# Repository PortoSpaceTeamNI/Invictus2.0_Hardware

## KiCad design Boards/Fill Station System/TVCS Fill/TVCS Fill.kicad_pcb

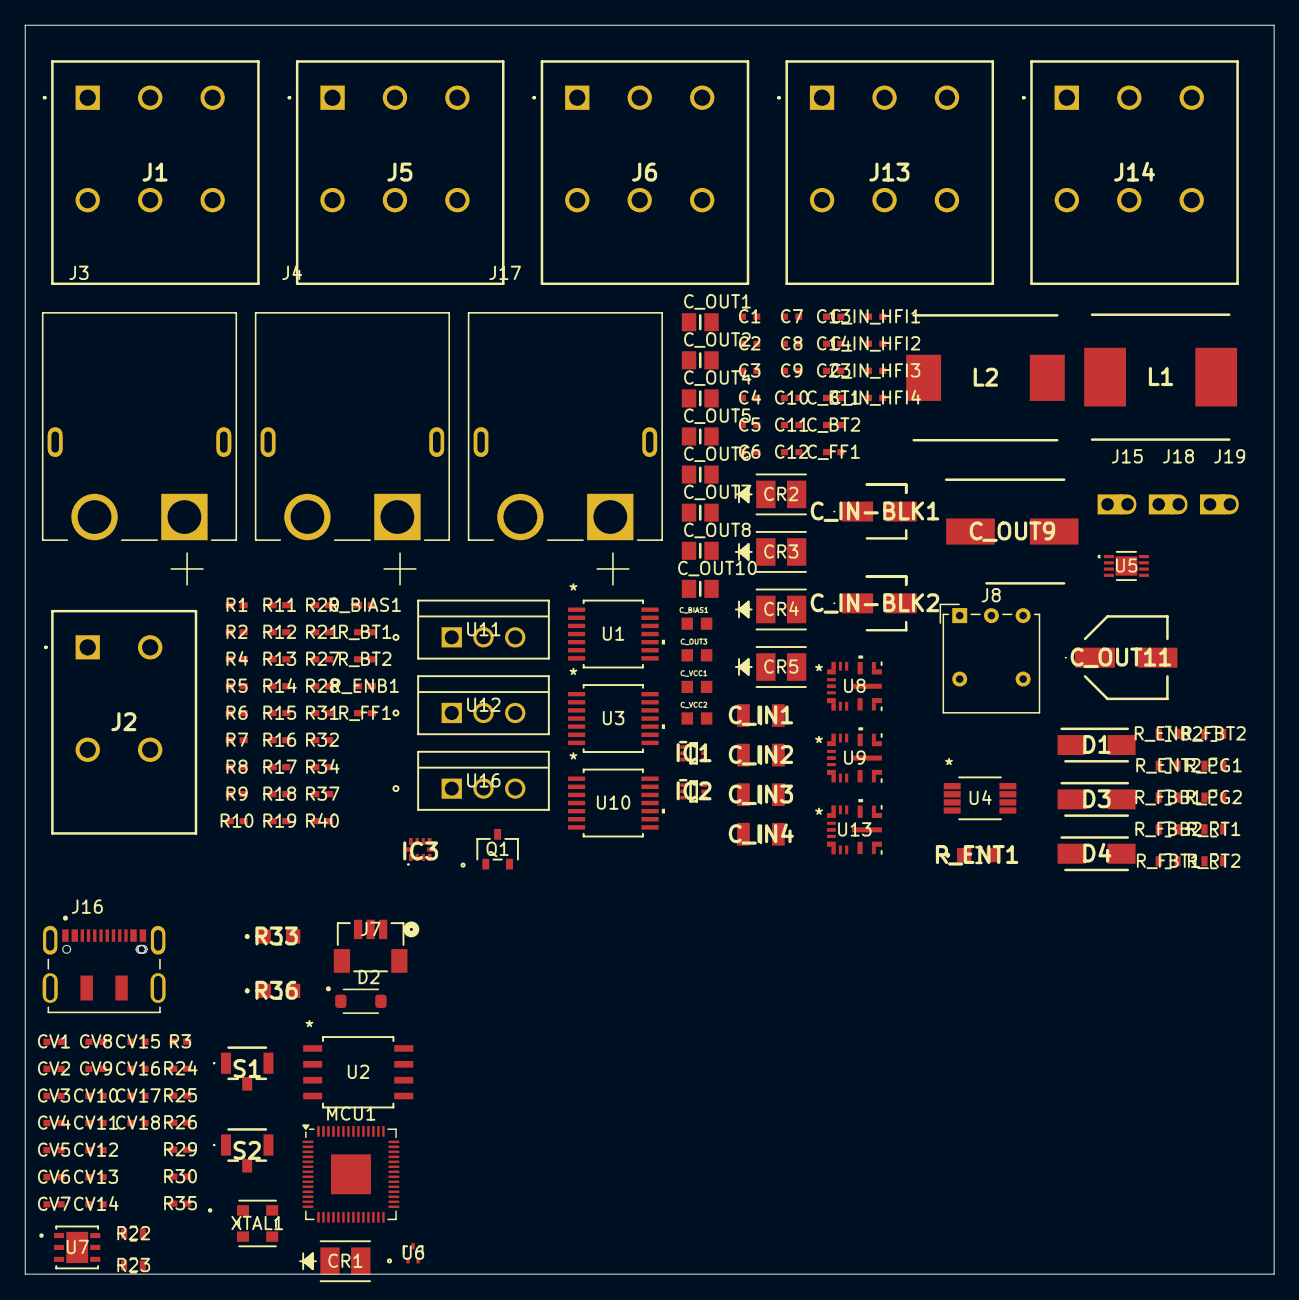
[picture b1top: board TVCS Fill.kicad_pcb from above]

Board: 6 copper layers, 100.0 x 100.0 mm, 162 parts (0 on the bottom side), 99 nets, no tracks yet.

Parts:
C1, C3, C9, C23: 100nF; Capacitor_0402
C2, C4, C5, C6, C7, C8, C10, C12, C13, C14: 10nF; Capacitor_0402
C11: 100 nF; Capacitor_0402
CR1, CR2, CR3, CR4, CR5: VLMC3100-GS08; LED_PLCC_VSMB
CV1, CV3, CV6, CV13, CV17: 1uF; Capacitor_0402
CV2, CV4, CV5, CV7, CV8, CV9, CV10, CV11, CV12, CV14, CV18: 100nF; Capacitor_0402
CV15, CV16: 4.7uF; Capacitor_0402
C_BIAS1: 1u; Capacitor_0603
C_BT1, C_BT2: 100n; Capacitor_0402
C_FF1: 22p; Capacitor_0402
C_IN1, C_IN2, C_IN3, C_IN4: 4.7u; Capacitor_1206
C_IN-BLK1, C_IN-BLK2: 10u; Capacitor_4mm
C_IN_HFI1, C_IN_HFI2, C_IN_HFI3, C_IN_HFI4: 100n; Capacitor_0402
C_OUT1, C_OUT2, C_OUT5, C_OUT7: 22u; Capacitor_0805
C_OUT3: 1u; Capacitor_0603
C_OUT4, C_OUT6, C_OUT8, C_OUT10: 10u; Capacitor_0805
C_OUT9: 560u; Capacitor_8mm
C_OUT11: 100u; Capacitor_6mm
C_VCC1, C_VCC2: 1u; Capacitor_0603
D1, D3, D4: RSX301L-30DDTE25; DIOM5026X220N
D2: PMEG2010ER; SODFL3517X110N
IC1, IC2: NSVT30010MXV6T1G; SOTFL50P160X60-6N
IC3: ADS1115IRUGR
J1, J5, J6, J13, J14: 1190298
J2: 1190297
J3, J4, J17: XT60PW-M; AMASS_XT60PW-M
J7: BM03B-SRSS-TBLFSN; CONN_BM03B-SRSS-TBLFSN_JST
J8: XT60PW-M; SW_Lever_1P2T_NKK_GW12LxH
J15, J18, J19: Conn_01x01_Socket; Pico_01pin
J16: DX07S016JA1R1500; JAE_DX07S016JA1R1500
L1: 15u; Inductor_10.1x10
L2: 10u; Inductor_11.5x10
MCU1: RP2040; QFN-56-1EP_7x7mm_P0.4mm_EP3.2x3.2mm
Q1: 2N7002H6327XTSA2; PG-SOT23-3-5_INF_MIN
R1, R2, R6, R7, R16, R18, R24, R25: 100; RES_0402
R3, R21, R26, R27, R28, R32, R35: 1k; RES_0402
R4: 200k; RES_0402
R5, R15, R19, R20, R31, R34, R40: 2k; RES_0402
R8: 120; RES_0402
R9, R10: 20K; RES_0402
R11, R12, R13: 10K; RES_0402
R14, R17, R29, R37: 10k; RES_0402
R22, R23: 27; RES_0603
R30: 665; RES_0402
R33, R36: 5k1; RES_0805
R_BIAS1: 10; RES_0402
R_BT1: 100; RES_0402
R_BT2: 50; RES_0402
R_ENB1: 35k; RES_0402
R_ENB2: 100k; RES_0603
R_ENT1: 400k; RES_0805
R_ENT2: 1.15M; RES_0603
R_FBB1: 24k9; RES_0603
R_FBB2: 9k09; RES_0603
R_FBT1, R_FBT2: 100K; RES_0603
R_FF1: 1k; RES_0402
R_PG1, R_PG2: 100K; RES_0603
R_RT1, R_RT2: 33k2; RES_0603
S1, S2: TL1017AABF160QG
U1, U3: MAX31856MUD+T; 21-0066J_14_MXM
U2: W25Q128JVSIQ TR; SOIC_208MIL_WIN
U4: PCA9306DP_118; TSSOP8_SOT505-1_NXP
U5: MAX485CSA+T; DFN8_2x3MC_MCH
U6: ESD7L5.0DT5G; SOT-723_0P85X1P25_ONS
U7: ST1L05APU33R; DFN_5APU33R_STM
U8: MCP9808T-E/MC; VQFN-HR14_RJR_TEX
U9: MAX31856MUD+T; VQFN-HR14_RJR_TEX
U10: LM61460AASQRJRRQ1; 21-0066J_14_MXM
U11, U12, U16: IRLZ44NPBF; PG-TO220-3_INF
U13: LM61460AASQRJRRQ1; VQFN-HR14_RJR_TEX
XTAL1: ASE-12.000MHZ-LC-T; ASE-3.2X2.5_ABR

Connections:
+3.3V: C5.2, C6.2, C7.2, C8.2, C12.2, C13.2, C14.1, CV5.1, CV6.1, CV7.1, CV8.1, CV9.1, CV10.1, CV11.1, CV12.1, CV13.1, CV14.1, CV16.2, CV18.1, MCU1.1 (IOVDD), MCU1.10 (IOVDD), MCU1.22 (IOVDD), MCU1.33 (IOVDD), MCU1.42 (IOVDD), MCU1.43 (ADC_AVDD), MCU1.44 (VREG_IN), MCU1.48 (USB_VDD), MCU1.49 (IOVDD), Q1.1 (G), R3.1, R11.1, R12.1, R13.2, R15.1, R19.1, R20.1, R29.2, R31.1, U1.5 (AVDD), U1.8 (DVDD), U2.8 (VCC), U3.5 (AVDD), U3.8 (DVDD), U4.2 (VREF1), U7.2 (V0), U8.8 (VDD), U9.5 (AVDD), U9.8 (DVDD), XTAL1.4 (VDD)
+5V: C11.1, CR2.2, CR3.2, CR4.2, CR5.2, IC3.8 (VDD), R4.2, R5.1, R9.1, R34.1, R40.1, U5.8 (VCC)
+12V: C_OUT3.1, C_OUT4.1, C_OUT6.1, C_OUT8.1, C_OUT10.1, C_OUT11.1, D1.1 (K), D3.1 (K), D4.1 (K), J3.2 (-), J4.2 (-), J5.1, J5.2, J13.1, J13.2, J14.1, J14.2, J17.2 (-), L2.2, R_FBT2.1, R_PG2.2
+16V: C_IN1.1, C_IN2.1, C_IN3.1, C_IN4.1, C_IN-BLK1.1, C_IN-BLK2.1, C_IN_HFI1.1, C_IN_HFI2.1, C_IN_HFI3.1, C_IN_HFI4.1, J8.2 (-), R_ENT1.2, R_ENT2.2, U10.8 (VIN1), U10.12 (VIN2), U13.8 (VIN1), U13.12 (VIN2)
/5V REG: C_OUT1.1, C_OUT2.1, C_OUT5.1, C_OUT7.1, C_OUT9.1, L1.2, R_BIAS1.2, R_FBT1.1, R_FF1.1, R_PG1.2
/ADC RDY: Q1.2 (S), R31.2
/ADC_AIN0: IC3.4 (AIN0), J5.3, J5.4
/ADC_AIN1: IC3.5 (AIN1), J13.3, J13.4
/ADC_AIN2: IC3.6 (AIN2), J14.3, J14.4
/DC.DC1 PGOOD: C_VCC2.1, R_PG2.1, U13.2 (VCC), U13.5 (PGOOD)
/DC.DC2 PGOOD: C_VCC1.1, R_PG1.1, U10.2 (VCC), U10.5 (PGOOD)
/RP2040 Standard/+5V: CV15.2, CV17.2, D2.C, U7.3 (V1)
/RP2040 Standard/GP27_ADC1: J15.1, MCU1.39 (GPIO27_ADC1)
/RP2040 Standard/GP28_ADC2: J18.1, MCU1.40 (GPIO28_ADC2)
/RP2040 Standard/GP29_ADC3: J19.1, MCU1.41 (GPIO29_ADC3)
/RP2040 Standard/MCU QSPI_SCLK: MCU1.52 (QSPI_SCLK), U2.6 (CLK)
/RP2040 Standard/MCU QSPI_SD0: MCU1.53 (QSPI_SD0), U2.5 (DI(IO0))
/RP2040 Standard/MCU QSPI_SD1: MCU1.55 (QSPI_SD1), U2.2 (DO(IO1))
/RP2040 Standard/MCU QSPI_SD2: MCU1.54 (QSPI_SD2), U2.3 (/WP(IO2))
/RP2040 Standard/MCU QSPI_SD3: MCU1.51 (QSPI_SD3), U2.7 (/HOLD_/RESET)
/RP2040 Standard/MCU QSPI_SS: MCU1.56 (QSPI_SS), R35.2, U2.1 (/CS)
/RP2040 Standard/USB_DM: J16.5 (D-), J16.8 (D-), R23.1, U6.1
/RP2040 Standard/USB_DP: J16.6 (D+), J16.7 (D+), R22.1, U6.2
/RP2040 Standard/~RST: R26.1, S1.2 (NO)
/RP2040 Standard/~USB_BOOT: R35.1, S2.2 (NO)
/RS_ENABLE: IC2.2 (B2), R12.2, U5.2 (*RE), U5.3 (DE)
/RS_RX: R11.2, U5.1 (RO)
/RS_TX: R13.1, U5.4 (DI)
/SPI_MISO: U1.11 (SDO), U3.11 (SDO), U9.11 (SDO)
/SPI_MOSI: U1.12 (SDI), U3.12 (SDI), U9.12 (SDI)
/SPI_SCK: U1.10 (SCK), U3.10 (SCK), U9.10 (SCK)
/TEMP ALERT: R15.2, U8.3 (ALERT)
/TEMP SDA I2C: R20.2, U8.1 (SDA)
/TEMP SDL I2C: R19.2, U8.2 (SCL)
/THERMO1 T+: J1.1, J1.2, R1.2
/THERMO1 T-: J1.3, J1.4, R2.2, U1.2 (BIAS)
/THERMO1_~CS: IC1.5 (B1), U1.9 (~CS)
/THERMO2 T+: J1.5, J1.6, R6.2
/THERMO2 T-: J6.1, J6.2, R7.2, U3.2 (BIAS)
/THERMO2_~CS: IC1.2 (B2), U3.9 (~CS)
/THERMO3 T+: J6.3, J6.4, R16.2
/THERMO3 T-: J6.5, J6.6, R18.2, U9.2 (BIAS)
/THERMO3_~CS: IC2.5 (B1), U9.9 (~CS)
/Valve Control 1: R17.1, U11.1 (G)
/Valve Control 2: R14.1, U12.1 (G)
/Valve Control 3: R37.1, U16.1 (G)
CRYSTAL: MCU1.20 (XIN), XTAL1.3 (OUTPUT)
GND: C2.2, C4.2, C5.1, C6.1, C7.1, C8.1, C10.2, C11.2, C12.1, C13.1, C14.2, C23.2, CR1.1, CV1.2, CV2.1, CV3.2, CV4.1, CV5.2, CV6.2, CV7.2, CV8.2, CV9.2, CV10.2, CV11.2, CV12.2, CV13.2, CV14.2, CV15.1, CV16.1, CV17.1, CV18.2, C_BIAS1.2, C_IN1.2, C_IN2.2, C_IN3.2, C_IN4.2, C_IN-BLK1.2, C_IN-BLK2.2, C_IN_HFI1.2, C_IN_HFI2.2, C_IN_HFI3.2, C_IN_HFI4.2, C_OUT1.2, C_OUT2.2, C_OUT3.2, C_OUT4.2, C_OUT5.2, C_OUT6.2, C_OUT7.2, C_OUT8.2, C_OUT9.2, C_OUT10.2, C_OUT11.2, C_VCC1.2, C_VCC2.2, IC1.3 (C1), IC1.6 (C2), IC2.3 (C1), IC2.6 (C2), IC3.1 (ADDR), IC3.3 (GND), IC3.7 (AIN3), J5.5, J5.6, J7.2, J8.1 (+), J13.5, J13.6, J14.5, J14.6, J16.1 (GND), J16.12 (GND), MCU1.19 (TESTEN), MCU1.57 (GND), R10.2, R14.2, R17.2, R33.1, R36.1, R37.2, R_ENB1.1, R_ENB2.1, R_FBB1.2, R_FBB2.2, R_RT1.1, R_RT2.1, S1.1 (COM), S1.G1, S2.1 (COM), S2.G1, U1.1 (AGND), U1.14 (DGND), U2.4 (GND), U3.1 (AGND), U3.14 (DGND), U4.1 (GND), U5.5 (GND), U6.3, U7.6 (GND), U7.7 (GND), U8.4 (GND), U8.5 (A2), U8.6 (A1), U8.7 (A0), U8.9 (EPAD), U9.1 (AGND), U9.14 (DGND), U10.3 (AGND), U10.9 (PGND1), U10.11 (PGND2), U11.3 (S), U12.3 (S), U13.1 (BIAS), U13.3 (AGND), U13.9 (PGND1), U13.11 (PGND2), U16.3 (S), XTAL1.2 (GND/CASE)
unnamed: CR1.2, R30.2
unnamed: CR2.1, R21.2
unnamed: CR3.1, R27.2
unnamed: CR4.1, R28.2
unnamed: CR5.1, R32.2
unnamed: C_FF1.1, R_FF1.2
unnamed: D1.2 (A), J4.1 (+), U12.2
unnamed: D2.A, J16.2 (VBUS), J16.11 (VBUS)
unnamed: D3.2 (A), J3.1 (+), U11.2
unnamed: D4.2 (A), J17.1 (+), U16.2
unnamed: IC1.4 (E1), R21.1
unnamed: IC1.1 (E2), R27.1
unnamed: IC2.4 (E1), R28.1
unnamed: IC2.1 (E2), R32.1
unnamed: IC3.2 (ALERT/RDY), Q1.3 (D), R5.2
unnamed: IC3.10 (SCL), R34.2, U4.6 (SCL2)
unnamed: IC3.9 (SDA), R40.2, U4.5 (SDA2)
unnamed: J2.1 (1.1), J2.2 (1.2), R8.1, R10.1, U5.7 (B)
unnamed: J2.3 (2.1), J2.4 (2.2), R8.2, R9.2, U5.6 (A)
unnamed: J7.1, R24.1
unnamed: J7.3, R25.1
unnamed: J16.3 (CC1), R36.2
unnamed: J16.9 (CC2), R33.2
unnamed: MCU1.37 (GPIO25), R30.1
unnamed: CV1.1, MCU1.26 (RUN), R3.2, R26.2
unnamed: MCU1.24 (SWCLK), R24.2
unnamed: MCU1.25 (SWD), R25.2
unnamed: MCU1.46 (USB_DM), R23.2
unnamed: MCU1.47 (USB_DP), R22.2
unnamed: CV2.2, CV3.1, CV4.2, MCU1.23 (DVDD), MCU1.45 (VREG_VOUT), MCU1.50 (DVDD)
unnamed: C1.1, R1.1, U1.4 (T+)
unnamed: C1.2, C2.1, R2.1, U1.3 (T-)
unnamed: C3.1, R6.1, U3.4 (T+)
unnamed: C3.2, C4.1, R7.1, U3.3 (T-)
unnamed: C23.1, R4.1, U4.7 (VREF2), U4.8 (EN)
unnamed: C9.1, R16.1, U9.4 (T+)
unnamed: C9.2, C10.1, R18.1, U9.3 (T-)
unnamed: C_BIAS1.1, R_BIAS1.1, U10.1 (BIAS)
unnamed: C_BT1.2, R_BT1.1, U10.14 (CBOOT)
unnamed: R_ENB1.2, R_ENT1.1, U10.7 (EN/SYNC)
unnamed: C_FF1.2, R_FBB1.1, R_FBT1.2, U10.4 (FB)
unnamed: R_BT1.2, U10.13 (RBOOT)
unnamed: R_RT1.2, U10.6 (RT)
unnamed: C_BT1.1, L1.1, U10.10 (SW)
unnamed: C_BT2.2, R_BT2.1, U13.14 (CBOOT)
unnamed: R_ENB2.2, R_ENT2.1, U13.7 (EN/SYNC)
unnamed: R_FBB2.1, R_FBT2.2, U13.4 (FB)
unnamed: R_BT2.2, U13.13 (RBOOT)
unnamed: R_RT2.2, U13.6 (RT)
unnamed: C_BT2.1, L2.1, U13.10 (SW)
unnamed: R29.1, XTAL1.1 (TRI-STATE(STBY))

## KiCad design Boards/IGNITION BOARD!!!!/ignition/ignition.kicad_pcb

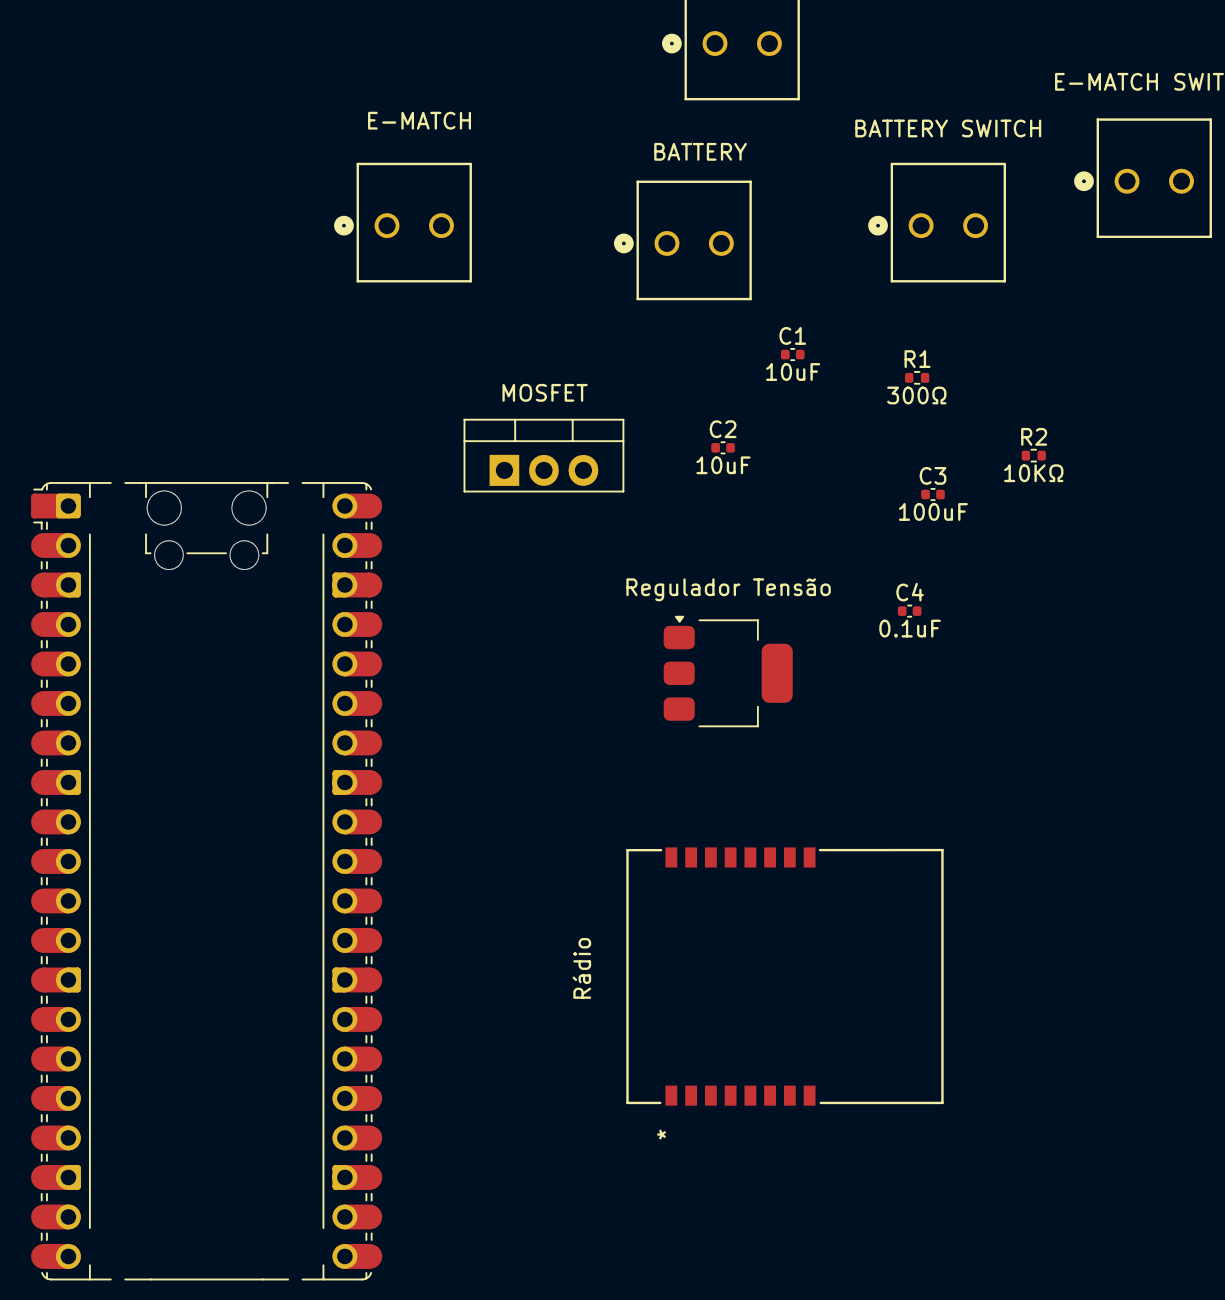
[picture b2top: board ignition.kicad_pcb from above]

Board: 2 copper layers, 15 parts (0 on the bottom side), 18 nets, no tracks yet.

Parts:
ARM KEY: Screw_Terminal_01x02; CONN_SD-39357-001_02P_MOL
BATTERY: Screw_Terminal_01x02; CONN_SD-39357-001_02P_MOL
BATTERY SWITCH: .; CONN_SD-39357-001_02P_MOL
C1, C2: 10uF; C_0402_1005Metric
C3: 100uF; C_0402_1005Metric
C4: 0.1uF; C_0402_1005Metric
E-MATCH: Ignitor; CONN_SD-39357-001_02P_MOL
E-MATCH SWITCH: Screw_Terminal_01x02; CONN_SD-39357-001_02P_MOL
MOSFET: IRLB8721PBF; TO-220-3_Vertical
R1: 300Ω; R_0402_1005Metric
R2: 10KΩ; R_0402_1005Metric
RASPBERRY PICO: RaspberryPi_Pico; RaspberryPi_Pico_Common_Unspecified
Regulador Tensão: AMS1117-3.3; SOT-223-3_TabPin2
Rádio: E28-2G4M27SX; E28-2G4M27SX_CGD

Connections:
GND: BATTERY.2, C1.2, C2.2, C3.2, C4.2, MOSFET.3 (S), R2.1, RASPBERRY PICO.3 (GND), RASPBERRY PICO.8 (GND), RASPBERRY PICO.13 (GND), RASPBERRY PICO.18 (GND), RASPBERRY PICO.23 (GND), RASPBERRY PICO.28 (GND), RASPBERRY PICO.38 (GND), Regulador Tensão.1 (GND), Rádio.2 (GND), Rádio.7 (GND), Rádio.10 (GND), Rádio.16 (GND)
unnamed: RASPBERRY PICO.14 (GPIO10), Rádio.8 (RX_EN)
unnamed: RASPBERRY PICO.15 (GPIO11), Rádio.9 (TX_EN)
unnamed: R1.2, RASPBERRY PICO.20 (GPIO15)
unnamed: RASPBERRY PICO.21 (GPIO16), Rádio.3 (MISO_TX)
unnamed: RASPBERRY PICO.22 (GPIO17), Rádio.6 (NSS_CTS)
unnamed: RASPBERRY PICO.24 (GPIO18), Rádio.5 (SCK_RTSN)
unnamed: RASPBERRY PICO.25 (GPIO19), Rádio.4 (MOSI_RX)
unnamed: RASPBERRY PICO.26 (GPIO20), Rádio.12 (BUSY)
unnamed: RASPBERRY PICO.27 (GPIO21), Rádio.13 (DIO1)
unnamed: RASPBERRY PICO.29 (GPIO22), Rádio.11 (NRESET)
unnamed: C2.1, C3.1, C4.1, RASPBERRY PICO.39 (VSYS), Regulador Tensão.2 (VO), Rádio.1 (VCC)
unnamed: ARM KEY.2, E-MATCH.1
unnamed: E-MATCH.2, MOSFET.2 (D)
unnamed: ARM KEY.1, E-MATCH SWITCH.2
unnamed: BATTERY.1, BATTERY SWITCH.1
unnamed: MOSFET.1 (G), R1.1, R2.2
unnamed: BATTERY SWITCH.2, C1.1, E-MATCH SWITCH.1, Regulador Tensão.3 (VI)

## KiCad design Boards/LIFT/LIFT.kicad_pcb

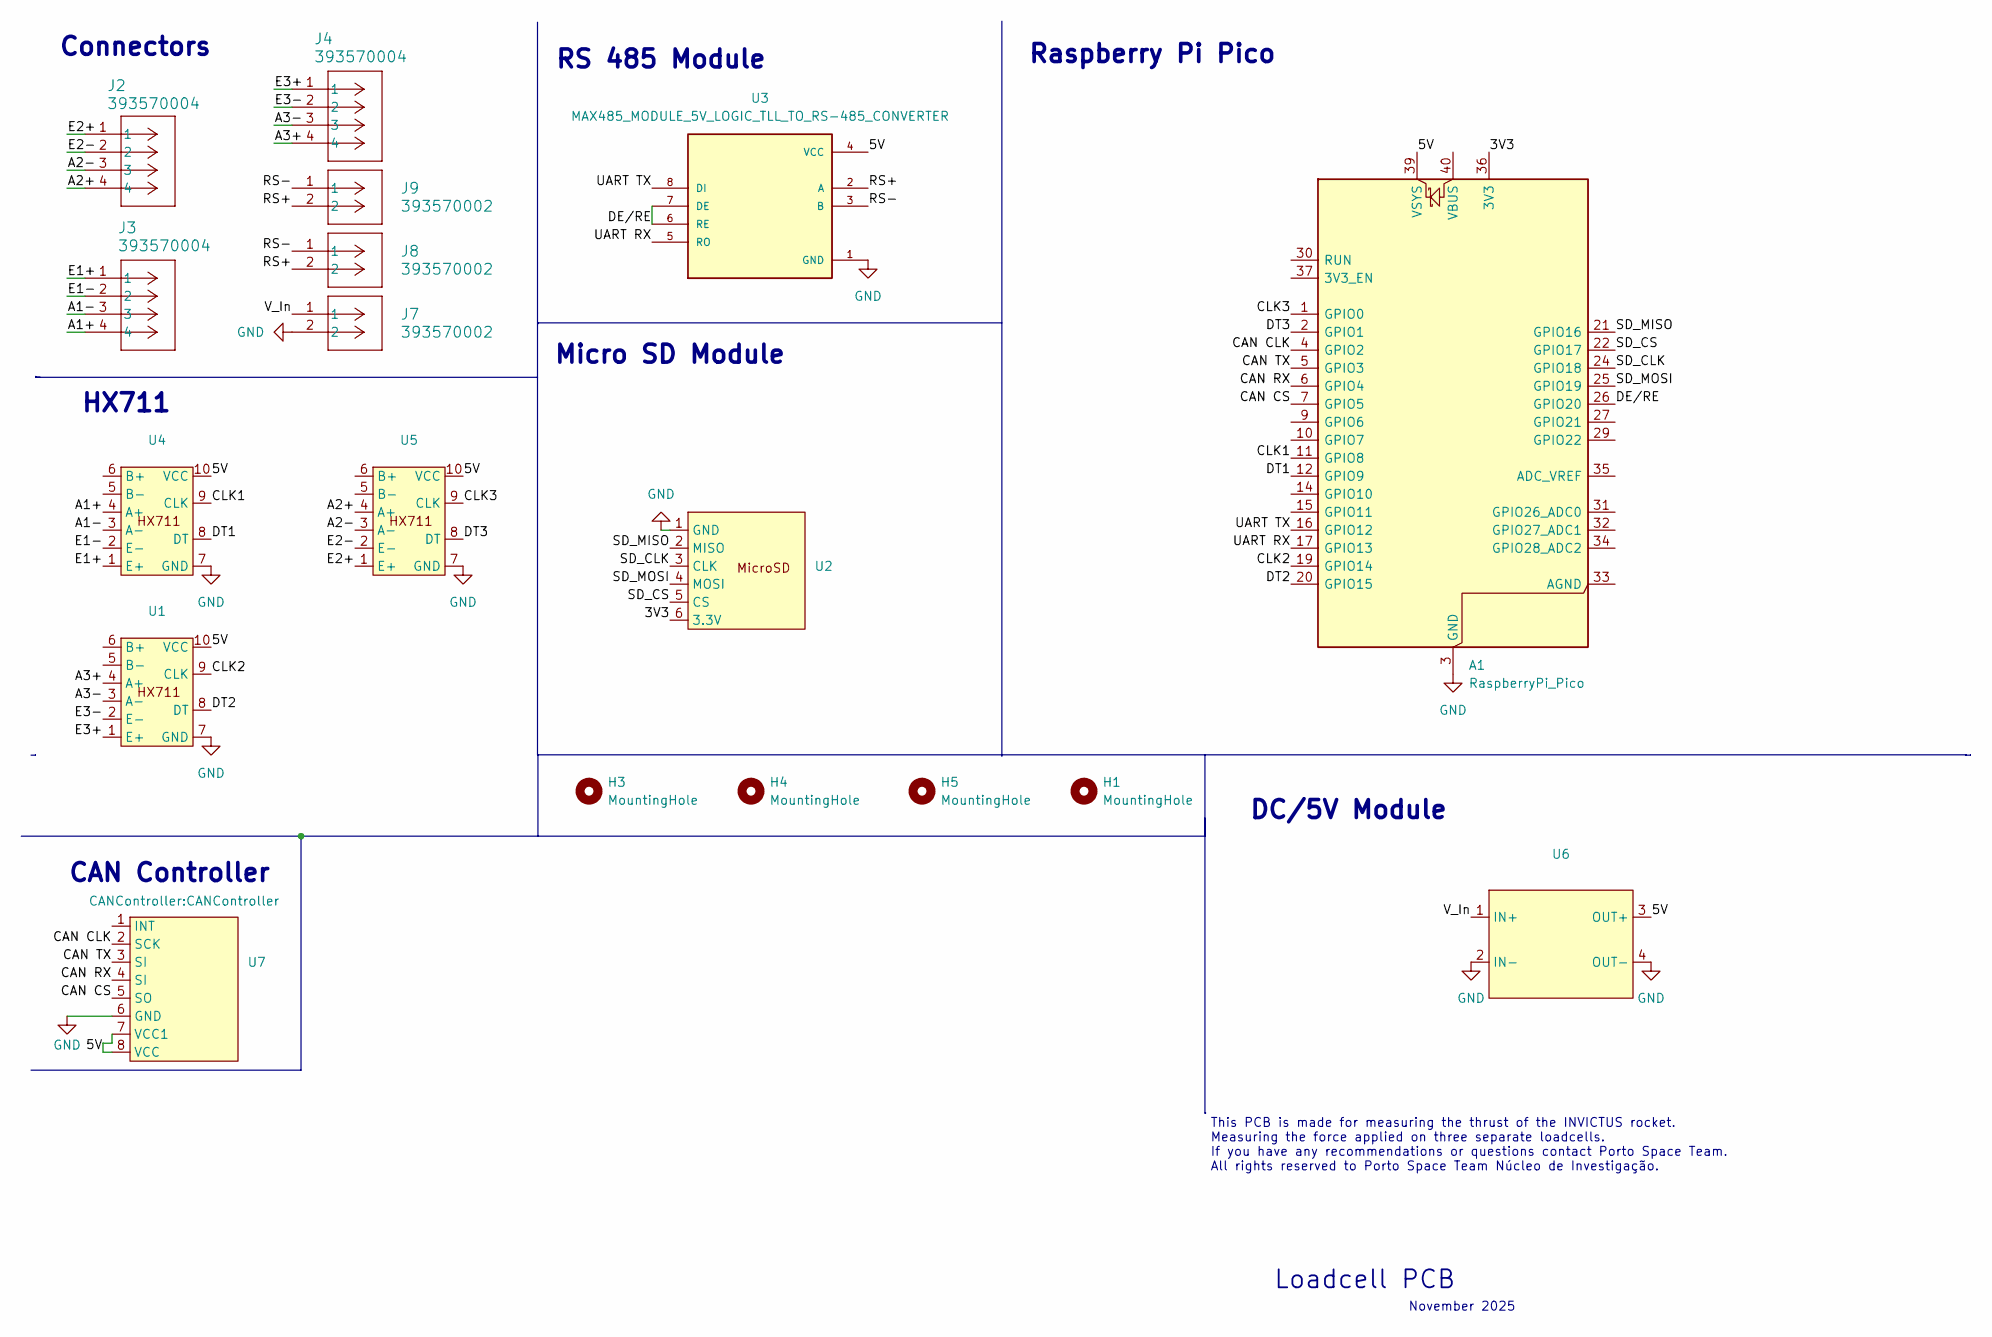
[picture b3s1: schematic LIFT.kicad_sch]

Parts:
A1: RaspberryPi_Pico; RaspberryPi_Pico_THT
H1, H3, H4, H5: MountingHole; MountingHole_3.2mm_M3
J2, J3, J4: 393570004; CONN_SD-39357-001_04P_MOL
J7, J8, J9: 393570002; CONN_SD-39357-001_02P_MOL
U1, U4, U5: HX711
U2: MicroSD Reader
U3: MAX485_MODULE_5V_LOGIC_TLL_TO_RS-485_CONVERTER; MODULE_MAX485_MODULE_5V_LOGIC_TLL_TO_RS-485_CONVERTER; PARTREV 1r0
U6: MiniDCDC
U7: CANController

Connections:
/3V3: A1.36 (3V3), U2.6 (3.3V)
/5V: A1.39 (VSYS), U1.10 (VCC), U3.4 (VCC), U4.10 (VCC), U5.10 (VCC), U6.3 (OUT+), U7.7 (VCC1), U7.8 (VCC)
/A1+: J3.4, U4.4 (A+)
/A1-: J3.3, U4.3 (A-)
/A2+: J2.4, U5.4 (A+)
/A2-: J2.3, U5.3 (A-)
/A3+: J4.4, U1.4 (A+)
/A3-: J4.3, U1.3 (A-)
/CAN CLK: A1.4 (GPIO2), U7.2 (SCK)
/CAN CS: A1.7 (GPIO5), U7.5 (SO)
/CAN RX: A1.6 (GPIO4), U7.4 (SI)
/CAN TX: A1.5 (GPIO3), U7.3 (SI)
/CLK1: A1.11 (GPIO8), U4.9 (CLK)
/CLK2: A1.19 (GPIO14), U1.9 (CLK)
/CLK3: A1.1 (GPIO0), U5.9 (CLK)
/DE/RE: A1.26 (GPIO20), U3.6 (RE), U3.7 (DE)
/DT1: A1.12 (GPIO9), U4.8 (DT)
/DT2: A1.20 (GPIO15), U1.8 (DT)
/DT3: A1.2 (GPIO1), U5.8 (DT)
/E1+: J3.1, U4.1 (E+)
/E1-: J3.2, U4.2 (E-)
/E2+: J2.1, U5.1 (E+)
/E2-: J2.2, U5.2 (E-)
/E3+: J4.1, U1.1 (E+)
/E3-: J4.2, U1.2 (E-)
/RS+: J8.2, J9.2, U3.2 (A)
/RS-: J8.1, J9.1, U3.3 (B)
/SD_CLK: A1.24 (GPIO18), U2.3 (CLK)
/SD_CS: A1.22 (GPIO17), U2.5 (CS)
/SD_MISO: A1.21 (GPIO16), U2.2 (MISO)
/SD_MOSI: A1.25 (GPIO19), U2.4 (MOSI)
/UART RX: A1.17 (GPIO13), U3.5 (RO)
/UART TX: A1.16 (GPIO12), U3.8 (DI)
/V_In: J7.1, U6.1 (IN+)
GND: A1.3 (GND), A1.8 (GND), A1.13 (GND), A1.18 (GND), A1.23 (GND), A1.28 (GND), A1.38 (GND), J7.2, U1.7 (GND), U2.1 (GND), U3.1 (GND), U4.7 (GND), U5.7 (GND), U6.2 (IN-), U6.4 (OUT-), U7.6 (GND)

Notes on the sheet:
HX711
Raspberry Pi Pico
This PCB is made for measuring the thrust of the INVICTUS rocket. Measuring the force applied on three separate loadcells. All rights reserved to Porto Space Team Núcleo de Investigação.
Loadcell PCB
Connectors
November 2025
DC/5V Module
Micro SD Module
CAN Controller
If you have any recommendations or questions contact Porto Space Team.
RS 485 Module

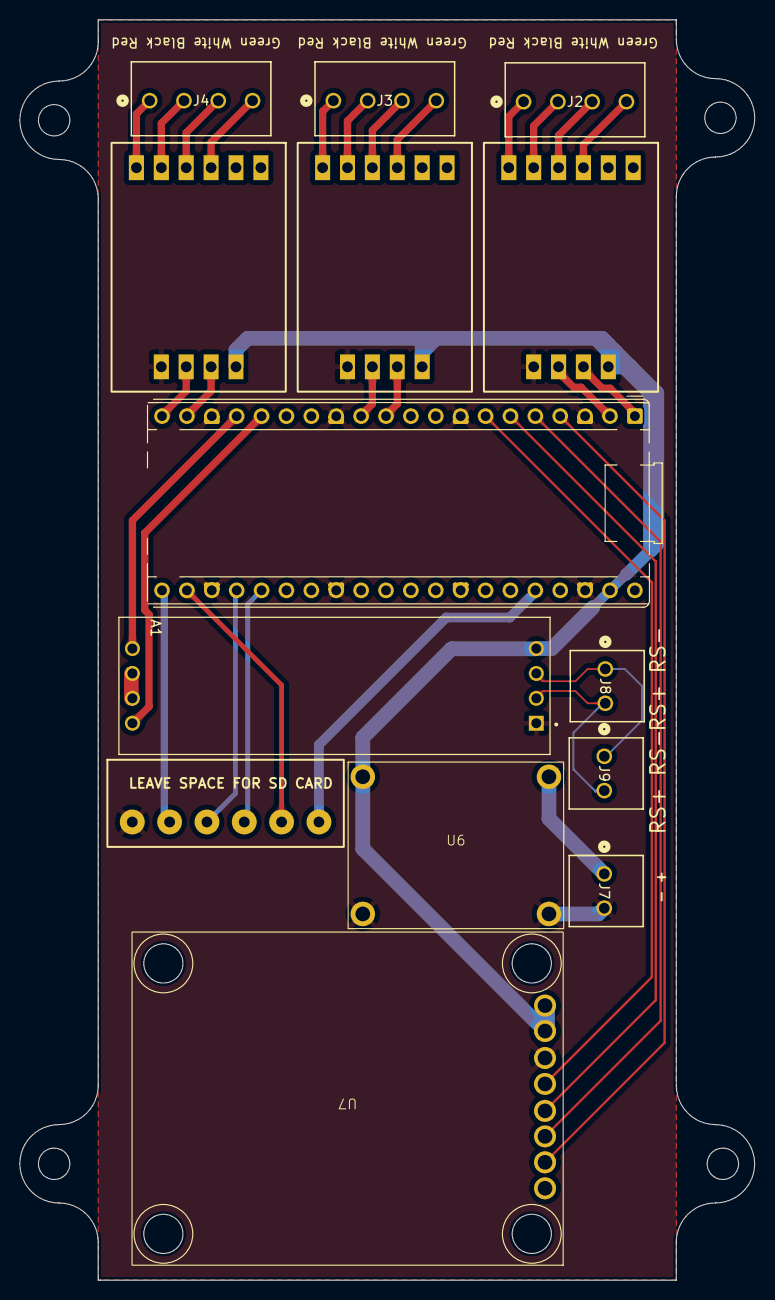
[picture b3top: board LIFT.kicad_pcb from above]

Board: 2 copper layers, 75.0 x 128.6 mm, 19 parts (0 on the bottom side), 35 nets.

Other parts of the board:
H1#2: MountingHole; MountingHole_3.2mm_M3

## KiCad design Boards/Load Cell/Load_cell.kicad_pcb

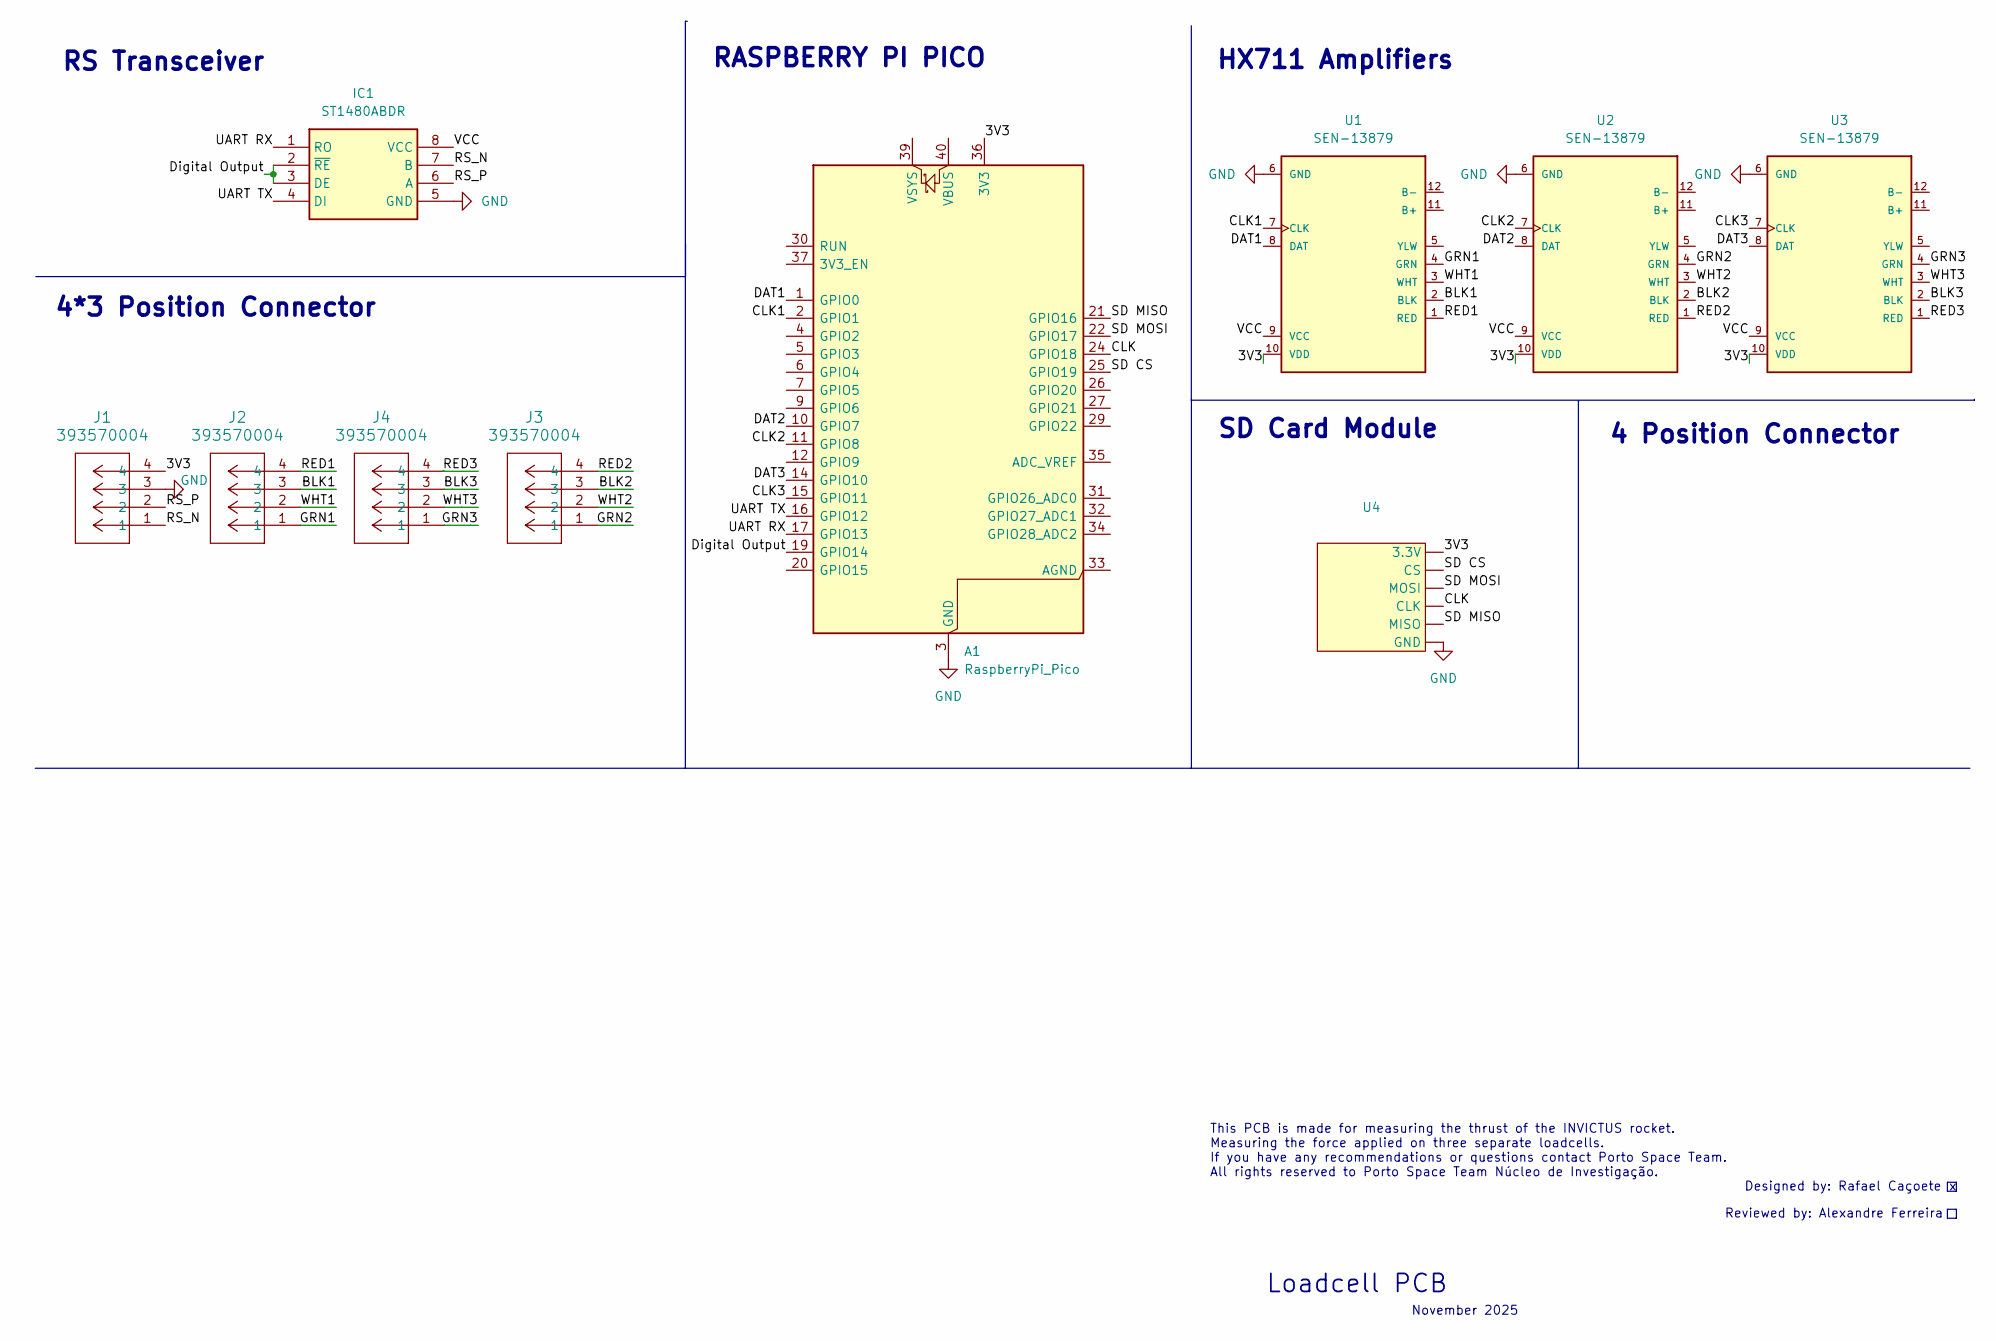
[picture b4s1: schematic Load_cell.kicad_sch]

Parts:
A1: RaspberryPi_Pico; RaspberryPi_Pico_Common_Unspecified
IC1: ST1480ABDR; SOIC127P600X175-8N; Mouser Part Number 511-ST1480ABDR
J1, J2, J3, J4: 393570004; CONN_SD-39357-001_04P_MOL
U1, U2, U3: SEN-13879; SPARKFUN_SEN-13879
U4: MicroSDCard

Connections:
/3V3: A1.36 (3V3), J1.4, U1.10 (VDD), U2.10 (VDD), U3.10 (VDD), U4.
/BLK1: J2.3, U1.2 (BLK)
/BLK2: J3.3, U2.2 (BLK)
/BLK3: J4.3, U3.2 (BLK)
/CLK: A1.24 (GPIO18), U4.
/CLK1: A1.2 (GPIO1), U1.7 (CLK)
/CLK2: A1.11 (GPIO8), U2.7 (CLK)
/CLK3: A1.15 (GPIO11), U3.7 (CLK)
/DAT1: A1.1 (GPIO0), U1.8 (DAT)
/DAT2: A1.10 (GPIO7), U2.8 (DAT)
/DAT3: A1.14 (GPIO10), U3.8 (DAT)
/Digital Output: A1.19 (GPIO14), IC1.2 (~RE), IC1.3 (DE)
/GRN1: J2.1, U1.4 (GRN)
/GRN2: J3.1, U2.4 (GRN)
/GRN3: J4.1, U3.4 (GRN)
/RED1: J2.4, U1.1 (RED)
/RED2: J3.4, U2.1 (RED)
/RED3: J4.4, U3.1 (RED)
/RS_N: IC1.7 (B), J1.1
/RS_P: IC1.6 (A), J1.2
/SD CS: A1.25 (GPIO19), U4.
/SD MISO: A1.21 (GPIO16), U4.
/SD MOSI: A1.22 (GPIO17), U4.
/UART RX: A1.17 (GPIO13), IC1.1 (RO)
/UART TX: A1.16 (GPIO12), IC1.4 (DI)
/VCC: IC1.8 (VCC), U1.9 (VCC), U2.9 (VCC), U3.9 (VCC)
/WHT1: J2.2, U1.3 (WHT)
/WHT2: J3.2, U2.3 (WHT)
/WHT3: J4.2, U3.3 (WHT)
GND: A1.3 (GND), A1.8 (GND), A1.13 (GND), A1.18 (GND), A1.23 (GND), A1.28 (GND), A1.38 (GND), IC1.5 (GND), J1.3, U1.6 (GND), U2.6 (GND), U3.6 (GND), U4.

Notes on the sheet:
RS Transceiver
HX711 Amplifiers
RASPBERRY PI PICO
This PCB is made for measuring the thrust of the INVICTUS rocket. Measuring the force applied on three separate loadcells. All rights reserved to Porto Space Team Núcleo de Investigação.
November 2025
SD Card Module
Designed by: Rafael Caçoete
4*3 Position Connector
Loadcell PCB
4 Position Connector
If you have any recommendations or questions contact Porto Space Team.
Reviewed by: Alexandre Ferreira

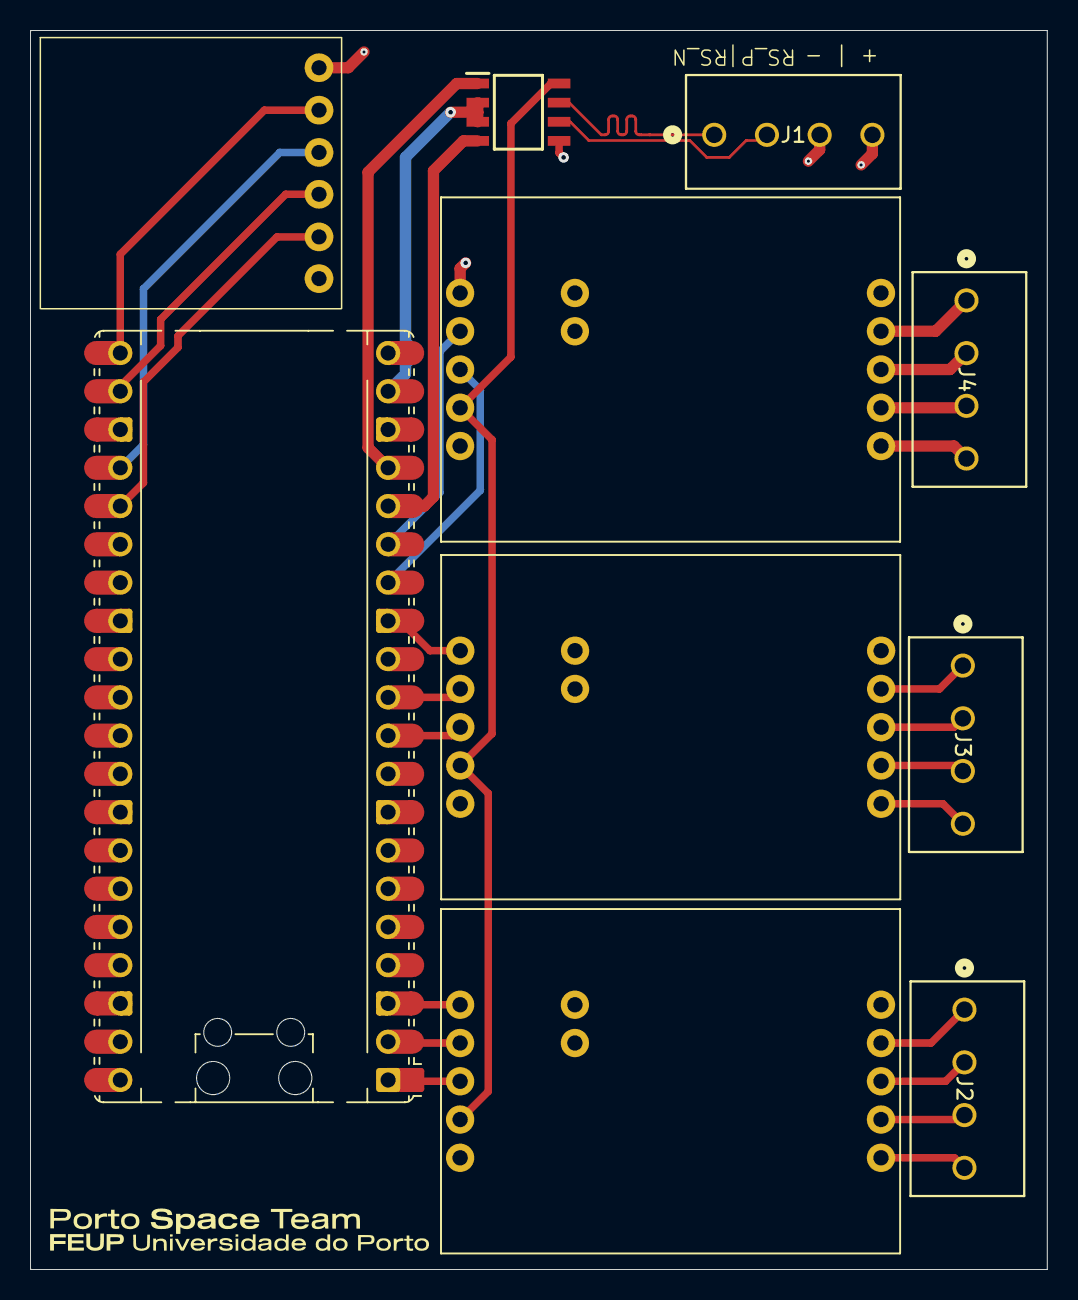
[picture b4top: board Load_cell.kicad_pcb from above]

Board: 4 copper layers, 67.5 x 82.2 mm, 9 parts (0 on the bottom side), 26 nets.

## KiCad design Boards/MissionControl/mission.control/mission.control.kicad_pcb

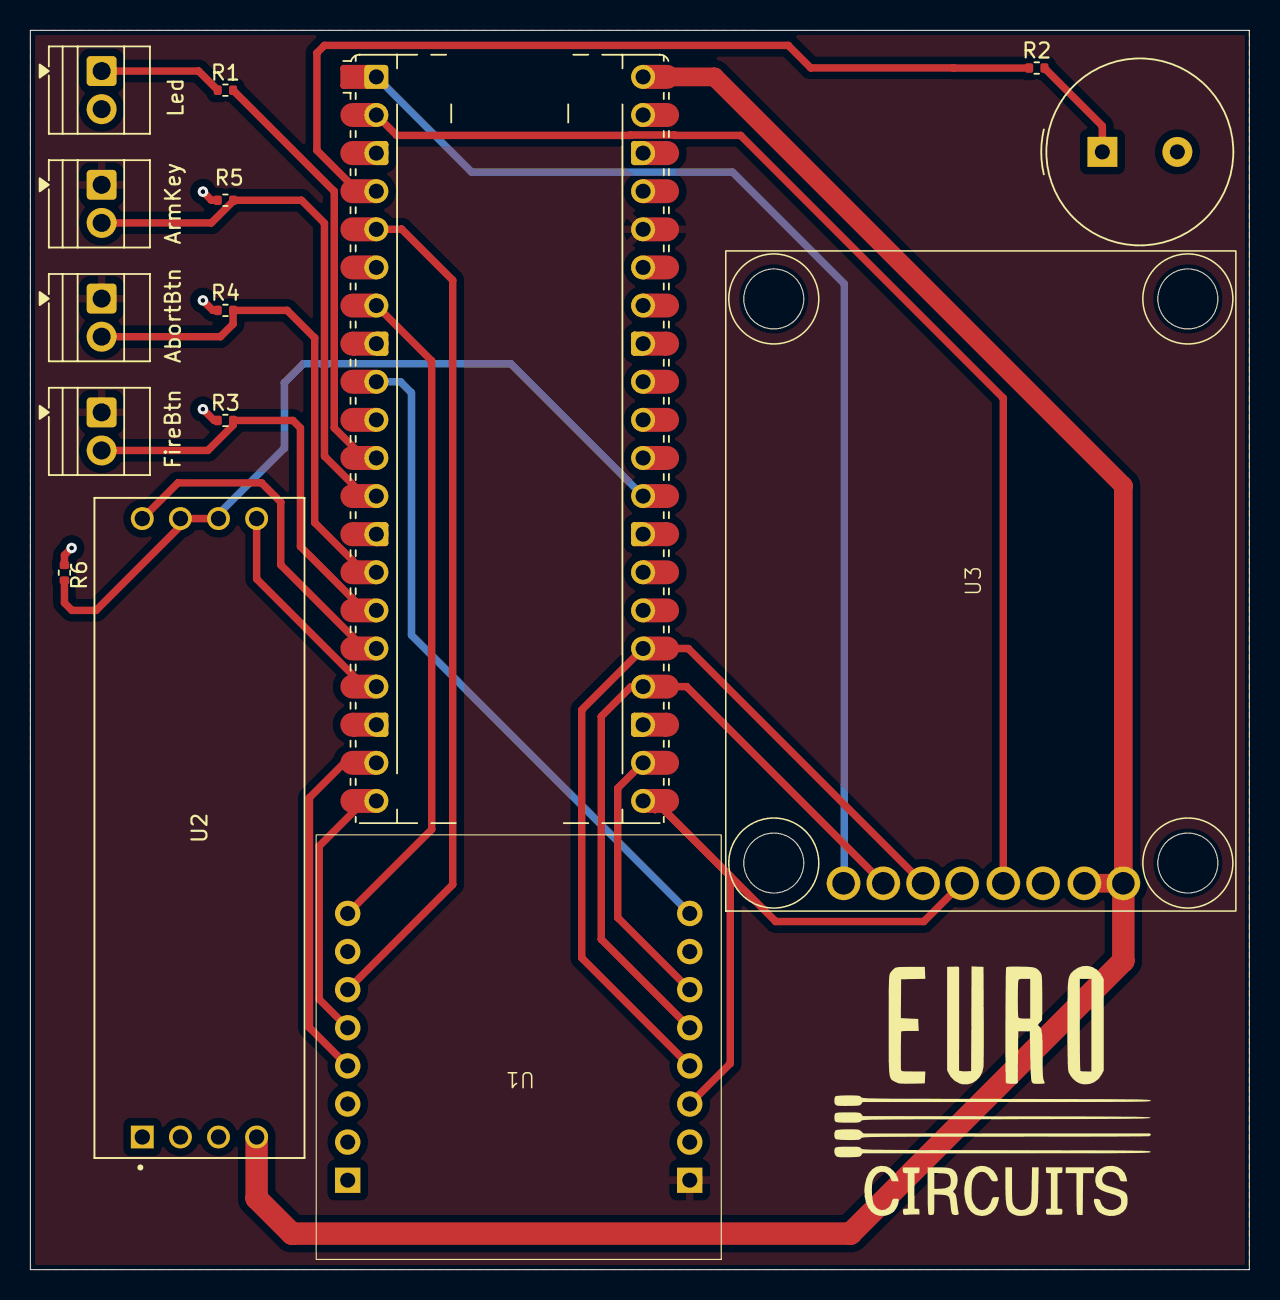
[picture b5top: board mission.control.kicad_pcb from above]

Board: 2 copper layers, 81.2 x 82.6 mm, 15 parts (0 on the bottom side), 24 nets.

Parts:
A1: RaspberryPi_Pico; RaspberryPi_Pico_Common_Unspecified
AbortBtn: .; TerminalBlock_Xinya_XY308-2.54-2P_1x02_P2.54mm_Horizontal
ArmKey: .; TerminalBlock_Xinya_XY308-2.54-2P_1x02_P2.54mm_Horizontal
BZ1: Buzzer; Buzzer_TDK_PS1240P02BT_D12.2mm_H6.5mm
FireBtn: .; TerminalBlock_Xinya_XY308-2.54-2P_1x02_P2.54mm_Horizontal
Led: .; TerminalBlock_Xinya_XY308-2.54-2P_1x02_P2.54mm_Horizontal
R1: 220Ω; R_0402_1005Metric
R2: 100Ω; R_0402_1005Metric
R3, R4, R5: 10KΩ; R_0402_1005Metric
R6: 1KΩ; R_0402_1005Metric
U1: E28-2G4M27SX; Radio_Module_PST
U2: MAX485_MODULE_5V_LOGIC_TLL_TO_RS-485_CONVERTER; MODULE_MAX485_MODULE_5V_LOGIC_TLL_TO_RS-485_CONVERTER
U3: CANController

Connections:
+3.3V: A1.36 (3V3), AbortBtn.1, ArmKey.1, FireBtn.1, U1.1 (VCC)
+5V: A1.40 (VBUS), U2.4 (VCC), U3.7 (VCC1), U3.8 (VCC)
/ABORT_SIGNAL: A1.14 (GPIO10), AbortBtn.2, R4.2
/ARM_SIGNAL: A1.12 (GPIO9), ArmKey.2, R5.2
/BUZZER_SIGNAL: A1.4 (GPIO2), R2.1
/CAN_CS: A1.2 (GPIO1), U3.5 (CS)
/CAN_INT: A1.1 (GPIO0), U3.1 (INT)
/FIRE_SIGNAL: A1.15 (GPIO11), FireBtn.2, R3.2
/LED_SIGNAL: A1.11 (GPIO8), R1.2
/RADIO_BUSY: A1.20 (GPIO15), U1.12 (BUSY)
/RADIO_CS: A1.22 (GPIO17), U1.6 (NSS_CTS)
/RADIO_DIO1: A1.19 (GPIO14), U1.13 (DIO1)
/RADIO_NRESET: A1.5 (GPIO3), U1.11 (NRESET)
/RADIO_RX_EN: A1.9 (GPIO6), U1.8 (RX_EN)
/RADIO_TX_EN: A1.7 (GPIO5), U1.9 (TX_EN)
/RS_DI: A1.16 (GPIO12), U2.8 (DI)
/RS_RO: A1.17 (GPIO13), U2.5 (RO)
/RS_TXEN: A1.29 (GPIO22), R6.1, U2.6 (RE), U2.7 (DE)
/SPI0_MISO: A1.21 (GPIO16), U1.3 (MISO_TX), U3.4 (SO)
/SPI0_MOSI: A1.25 (GPIO19), U1.4 (MOSI_RX), U3.3 (SI)
/SPI0_SCK: A1.24 (GPIO18), U1.5 (SCK_RTSN), U3.2 (SCK)
GND: A1.3 (GND), A1.8 (GND), A1.13 (GND), A1.18 (GND), A1.23 (GND), A1.28 (GND), A1.38 (GND), BZ1.2 (-), Led.2, R3.1, R4.1, R5.1, R6.2, U1.2 (GND), U1.7 (GND), U1.10 (GND), U1.16 (GND), U2.1 (GND), U3.6 (GND)
unnamed: BZ1.1 (+), R2.2
unnamed: Led.1, R1.1
